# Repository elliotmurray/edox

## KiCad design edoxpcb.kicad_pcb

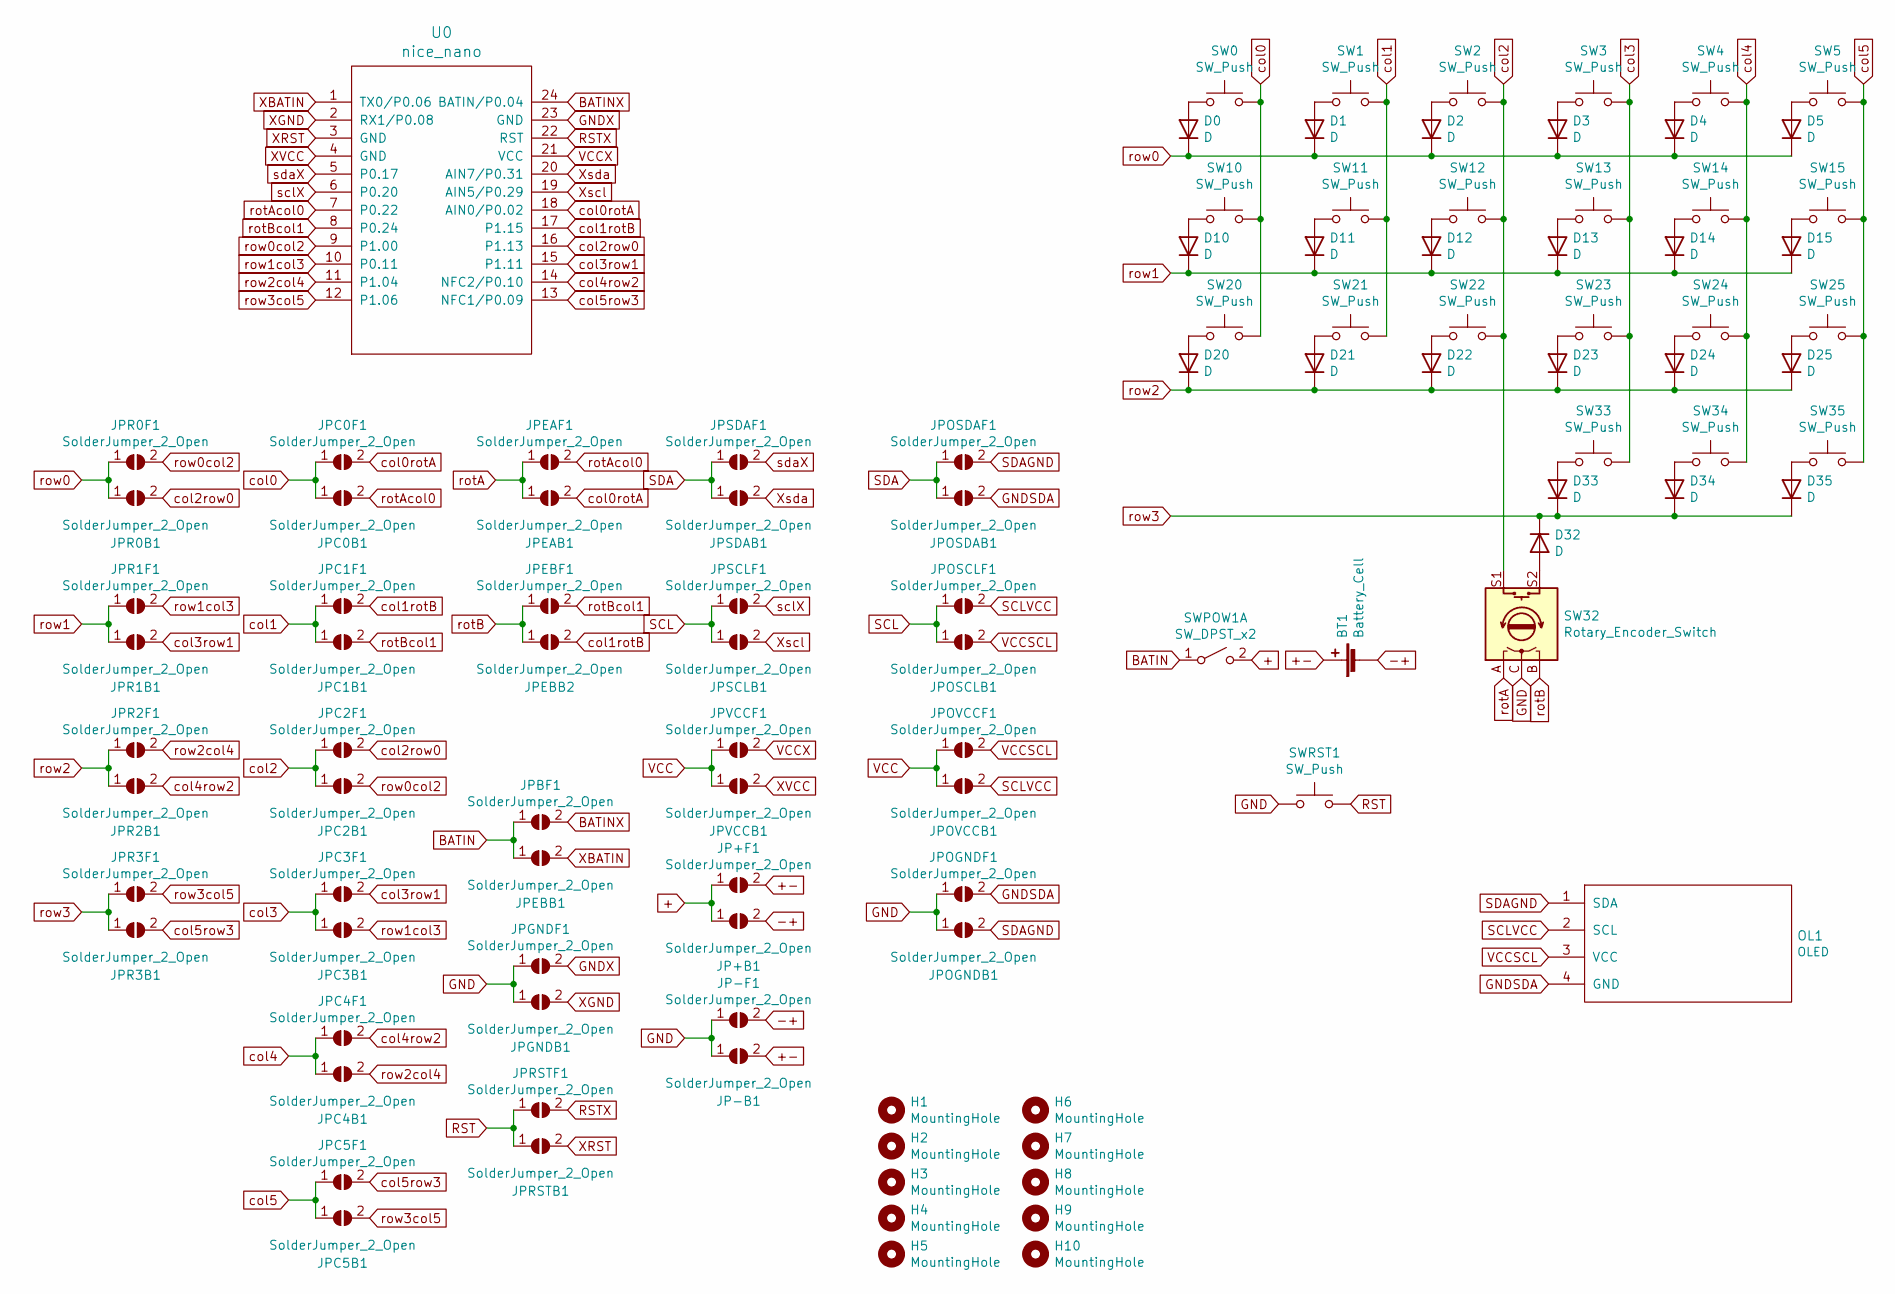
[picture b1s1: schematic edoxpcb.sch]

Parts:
BT1: Battery_Cell; jst_ph
D0, D1, D2, D3, D4, D5, D10, D11, D12, D13, D14, D15, D20, D21, D22, D23, D24, D25, D32, D33, D34, D35: D; D3_TH_SMD
H1, H2, H3, H4, H5: MountingHole; spacer_m2
H6, H7, H8, H9, H10: MountingHole; MountingHole_2.2mm_M2
JP+B1: SolderJumper_2_Open; SolderJumper-2_P1.3mm_Open_RoundedPad1.0x1.5mm
JP+F1: SolderJumper_2_Open; SolderJumper-2_P1.3mm_Open_RoundedPad1.0x1.5mm
JP-B1: SolderJumper_2_Open; SolderJumper-2_P1.3mm_Open_RoundedPad1.0x1.5mm
JP-F1: SolderJumper_2_Open; SolderJumper-2_P1.3mm_Open_RoundedPad1.0x1.5mm
JPBF1: SolderJumper_2_Open; SolderJumper-2_P1.3mm_Open_RoundedPad1.0x1.5mm
JPC0B1, JPC0F1, JPC1B1, JPC1F1, JPC2B1, JPC2F1, JPC3B1, JPC3F1, JPC4B1, JPC4F1, JPC5B1, JPC5F1: SolderJumper_2_Open; SolderJumper-2_P1.3mm_Open_RoundedPad1.0x1.5mm
JPEAB1: SolderJumper_2_Open; SolderJumper-2_P1.3mm_Open_RoundedPad1.0x1.5mm
JPEAF1: SolderJumper_2_Open; SolderJumper-2_P1.3mm_Open_RoundedPad1.0x1.5mm
JPEBB1, JPEBB2: SolderJumper_2_Open; SolderJumper-2_P1.3mm_Open_RoundedPad1.0x1.5mm
JPEBF1: SolderJumper_2_Open; SolderJumper-2_P1.3mm_Open_RoundedPad1.0x1.5mm
JPGNDB1: SolderJumper_2_Open; SolderJumper-2_P1.3mm_Open_RoundedPad1.0x1.5mm
JPGNDF1: SolderJumper_2_Open; SolderJumper-2_P1.3mm_Open_RoundedPad1.0x1.5mm
JPOGNDB1: SolderJumper_2_Open; SolderJumper-2_P1.3mm_Open_RoundedPad1.0x1.5mm
JPOGNDF1: SolderJumper_2_Open; SolderJumper-2_P1.3mm_Open_RoundedPad1.0x1.5mm
JPOSCLB1: SolderJumper_2_Open; SolderJumper-2_P1.3mm_Open_RoundedPad1.0x1.5mm
JPOSCLF1: SolderJumper_2_Open; SolderJumper-2_P1.3mm_Open_RoundedPad1.0x1.5mm
JPOSDAB1: SolderJumper_2_Open; SolderJumper-2_P1.3mm_Open_RoundedPad1.0x1.5mm
JPOSDAF1: SolderJumper_2_Open; SolderJumper-2_P1.3mm_Open_RoundedPad1.0x1.5mm
JPOVCCB1: SolderJumper_2_Open; SolderJumper-2_P1.3mm_Open_RoundedPad1.0x1.5mm
JPOVCCF1: SolderJumper_2_Open; SolderJumper-2_P1.3mm_Open_RoundedPad1.0x1.5mm
JPR0B1, JPR0F1, JPR1B1, JPR1F1, JPR2B1, JPR2F1, JPR3B1, JPR3F1: SolderJumper_2_Open; SolderJumper-2_P1.3mm_Open_RoundedPad1.0x1.5mm
JPRSTB1: SolderJumper_2_Open; SolderJumper-2_P1.3mm_Open_RoundedPad1.0x1.5mm
JPRSTF1: SolderJumper_2_Open; SolderJumper-2_P1.3mm_Open_RoundedPad1.0x1.5mm
JPSCLB1: SolderJumper_2_Open; SolderJumper-2_P1.3mm_Open_RoundedPad1.0x1.5mm
JPSCLF1: SolderJumper_2_Open; SolderJumper-2_P1.3mm_Open_RoundedPad1.0x1.5mm
JPSDAB1: SolderJumper_2_Open; SolderJumper-2_P1.3mm_Open_RoundedPad1.0x1.5mm
JPSDAF1: SolderJumper_2_Open; SolderJumper-2_P1.3mm_Open_RoundedPad1.0x1.5mm
JPVCCB1: SolderJumper_2_Open; SolderJumper-2_P1.3mm_Open_RoundedPad1.0x1.5mm
JPVCCF1: SolderJumper_2_Open; SolderJumper-2_P1.3mm_Open_RoundedPad1.0x1.5mm
OL1: OLED
SW0, SW1, SW2, SW3, SW4, SW5, SW10, SW11, SW12, SW13, SW14, SW15, SW20, SW21, SW22, SW23, SW24, SW25, SW33, SW34, SW35: SW_Push; mx_hot_reverse
SW32: Rotary_Encoder_Switch; RotaryEncoder_Alps_EC11E-Switch_Vertical_H20mm
SWPOW1: SW_DPST_x2; SW_CuK_JS202011AQN_DPDT_Angled
SWRST1: SW_Push; ResetSW
U0: nice_nano; nicenano

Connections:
+: JP+B1.1 (A), JP+F1.1 (A), SWPOW1.2 (B)
+-: BT1.1 (+), JP+F1.2 (B), JP-B1.2 (B)
-+: BT1.2 (-), JP+B1.2 (B), JP-F1.2 (B)
BATIN: JPBF1.1 (A), JPEBB1.1 (A), SWPOW1.1 (A)
BATINX: JPBF1.2 (B), U0.24 (BATIN/P0.04)
GND: JP-B1.1 (A), JP-F1.1 (A), JPGNDB1.1 (A), JPGNDF1.1 (A), JPOGNDB1.1 (A), JPOGNDF1.1 (A), SW32.C, SWRST1.1
GNDSDA: JPOGNDF1.2 (B), JPOSDAB1.2 (B), OL1.4 (GND)
GNDX: JPGNDF1.2 (B), U0.23 (GND)
unnamed: D0.2 (A), SW0.1
unnamed: D1.2 (A), SW1.1
unnamed: D2.2 (A), SW2.1
unnamed: D3.2 (A), SW3.1
unnamed: D4.2 (A), SW4.1
unnamed: D5.2 (A), SW5.1
unnamed: D10.2 (A), SW10.1
unnamed: D11.2 (A), SW11.1
unnamed: D12.2 (A), SW12.1
unnamed: D13.2 (A), SW13.1
unnamed: D14.2 (A), SW14.1
unnamed: D15.2 (A), SW15.1
unnamed: D20.2 (A), SW20.1
unnamed: D21.2 (A), SW21.1
unnamed: D22.2 (A), SW22.1
unnamed: D23.2 (A), SW23.1
unnamed: D24.2 (A), SW24.1
unnamed: D25.2 (A), SW25.1
unnamed: D32.2 (A), SW32.S2
unnamed: D33.2 (A), SW33.1
unnamed: D34.2 (A), SW34.1
unnamed: D35.2 (A), SW35.1
RST: JPRSTB1.1 (A), JPRSTF1.1 (A), SWRST1.2
RSTX: JPRSTF1.2 (B), U0.22 (RST)
SCL: JPOSCLB1.1 (A), JPOSCLF1.1 (A), JPSCLB1.1 (A), JPSCLF1.1 (A)
SCLVCC: JPOSCLF1.2 (B), JPOVCCB1.2 (B), OL1.2 (SCL)
SDA: JPOSDAB1.1 (A), JPOSDAF1.1 (A), JPSDAB1.1 (A), JPSDAF1.1 (A)
SDAGND: JPOGNDB1.2 (B), JPOSDAF1.2 (B), OL1.1 (SDA)
VCC: JPOVCCB1.1 (A), JPOVCCF1.1 (A), JPVCCB1.1 (A), JPVCCF1.1 (A)
VCCSCL: JPOSCLB1.2 (B), JPOVCCF1.2 (B), OL1.3 (VCC)
VCCX: JPVCCF1.2 (B), U0.21 (VCC)
XBATIN: JPEBB1.2 (B), U0.1 (TX0/P0.06)
XGND: JPGNDB1.2 (B), U0.2 (RX1/P0.08)
XRST: JPRSTB1.2 (B), U0.3 (GND)
XVCC: JPVCCB1.2 (B), U0.4 (GND)
Xscl: JPSCLB1.2 (B), U0.19 (AIN5/P0.29)
Xsda: JPSDAB1.2 (B), U0.20 (AIN7/P0.31)
col0: JPC0B1.1 (A), JPC0F1.1 (A), SW0.2, SW10.2, SW20.2
col0rotA: JPC0F1.2 (B), JPEAB1.2 (B), U0.18 (AIN0/P0.02)
col1: JPC1B1.1 (A), JPC1F1.1 (A), SW1.2, SW11.2, SW21.2
col1rotB: JPC1F1.2 (B), JPEBB2.2 (B), U0.17 (P1.15)
col2: JPC2B1.1 (A), JPC2F1.1 (A), SW2.2, SW12.2, SW22.2, SW32.S1
col2row0: JPC2F1.2 (B), JPR0B1.2 (B), U0.16 (P1.13)
col3: JPC3B1.1 (A), JPC3F1.1 (A), SW3.2, SW13.2, SW23.2, SW33.2
col3row1: JPC3F1.2 (B), JPR1B1.2 (B), U0.15 (P1.11)
col4: JPC4B1.1 (A), JPC4F1.1 (A), SW4.2, SW14.2, SW24.2, SW34.2
col4row2: JPC4F1.2 (B), JPR2B1.2 (B), U0.14 (NFC2/P0.10)
col5: JPC5B1.1 (A), JPC5F1.1 (A), SW5.2, SW15.2, SW25.2, SW35.2
col5row3: JPC5F1.2 (B), JPR3B1.2 (B), U0.13 (NFC1/P0.09)
rotA: JPEAB1.1 (A), JPEAF1.1 (A), SW32.A
rotAcol0: JPC0B1.2 (B), JPEAF1.2 (B), U0.7 (P0.22)
rotB: JPEBB2.1 (A), JPEBF1.1 (A), SW32.B
rotBcol1: JPC1B1.2 (B), JPEBF1.2 (B), U0.8 (P0.24)
row0: D0.1 (K), D1.1 (K), D2.1 (K), D3.1 (K), D4.1 (K), D5.1 (K), JPR0B1.1 (A), JPR0F1.1 (A)
row0col2: JPC2B1.2 (B), JPR0F1.2 (B), U0.9 (P1.00)
row1: D10.1 (K), D11.1 (K), D12.1 (K), D13.1 (K), D14.1 (K), D15.1 (K), JPR1B1.1 (A), JPR1F1.1 (A)
row1col3: JPC3B1.2 (B), JPR1F1.2 (B), U0.10 (P0.11)
row2: D20.1 (K), D21.1 (K), D22.1 (K), D23.1 (K), D24.1 (K), D25.1 (K), JPR2B1.1 (A), JPR2F1.1 (A)
row2col4: JPC4B1.2 (B), JPR2F1.2 (B), U0.11 (P1.04)
row3: D32.1 (K), D33.1 (K), D34.1 (K), D35.1 (K), JPR3B1.1 (A), JPR3F1.1 (A)
row3col5: JPC5B1.2 (B), JPR3F1.2 (B), U0.12 (P1.06)
sclX: JPSCLF1.2 (B), U0.6 (P0.20)
sdaX: JPSDAF1.2 (B), U0.5 (P0.17)

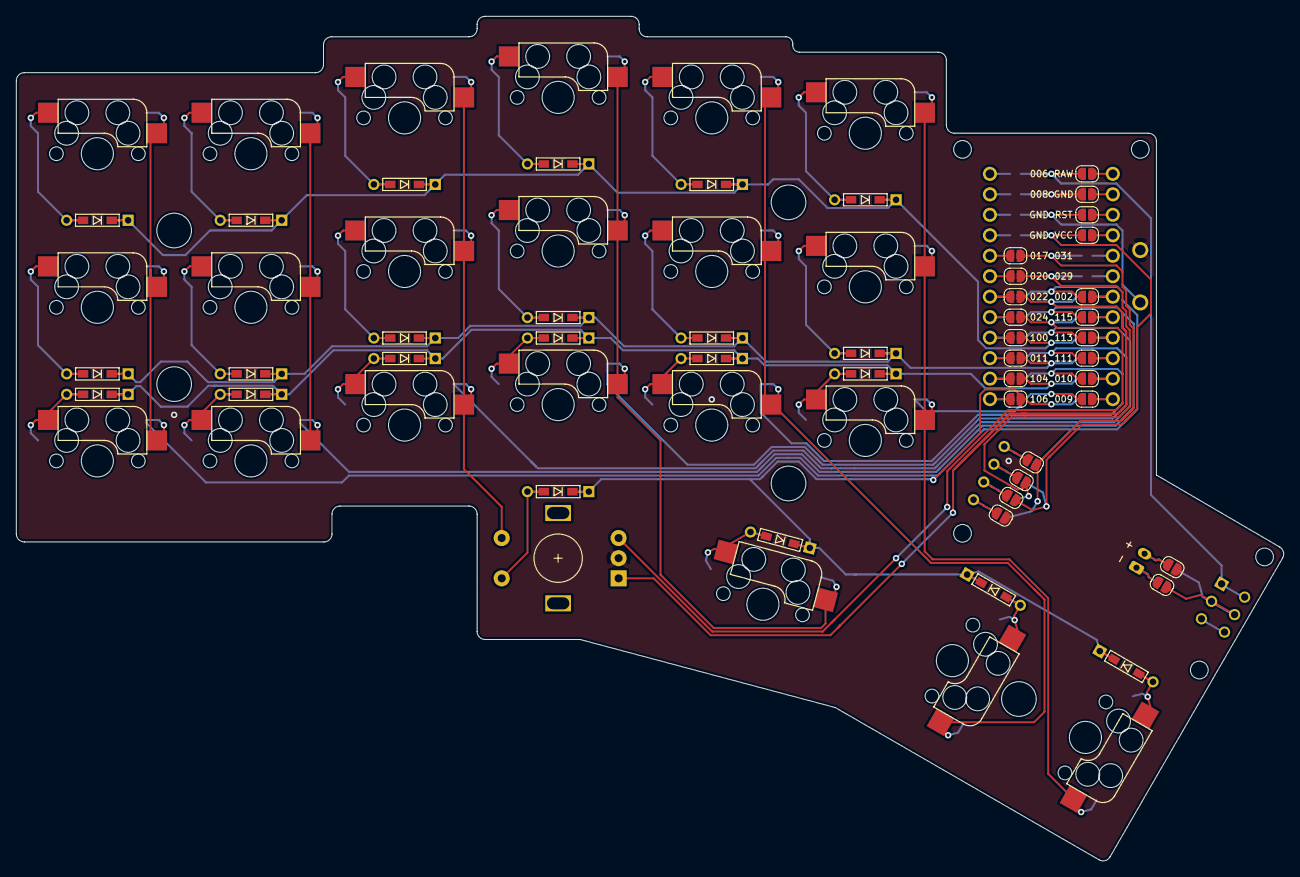
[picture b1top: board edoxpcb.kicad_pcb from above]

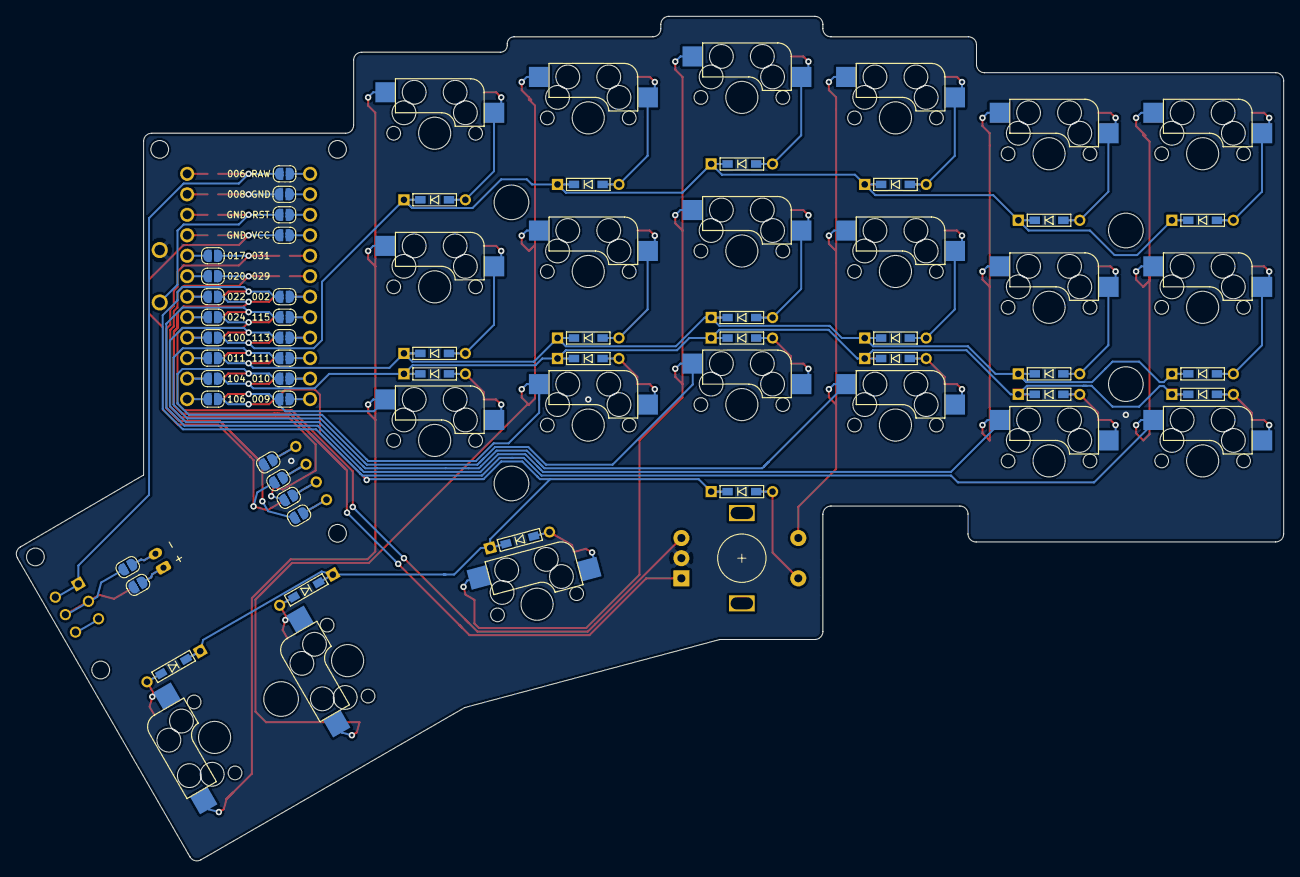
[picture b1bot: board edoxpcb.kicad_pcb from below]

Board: 2 copper layers, 157.2 x 104.7 mm, 107 parts (26 on the bottom side), 71 nets.
